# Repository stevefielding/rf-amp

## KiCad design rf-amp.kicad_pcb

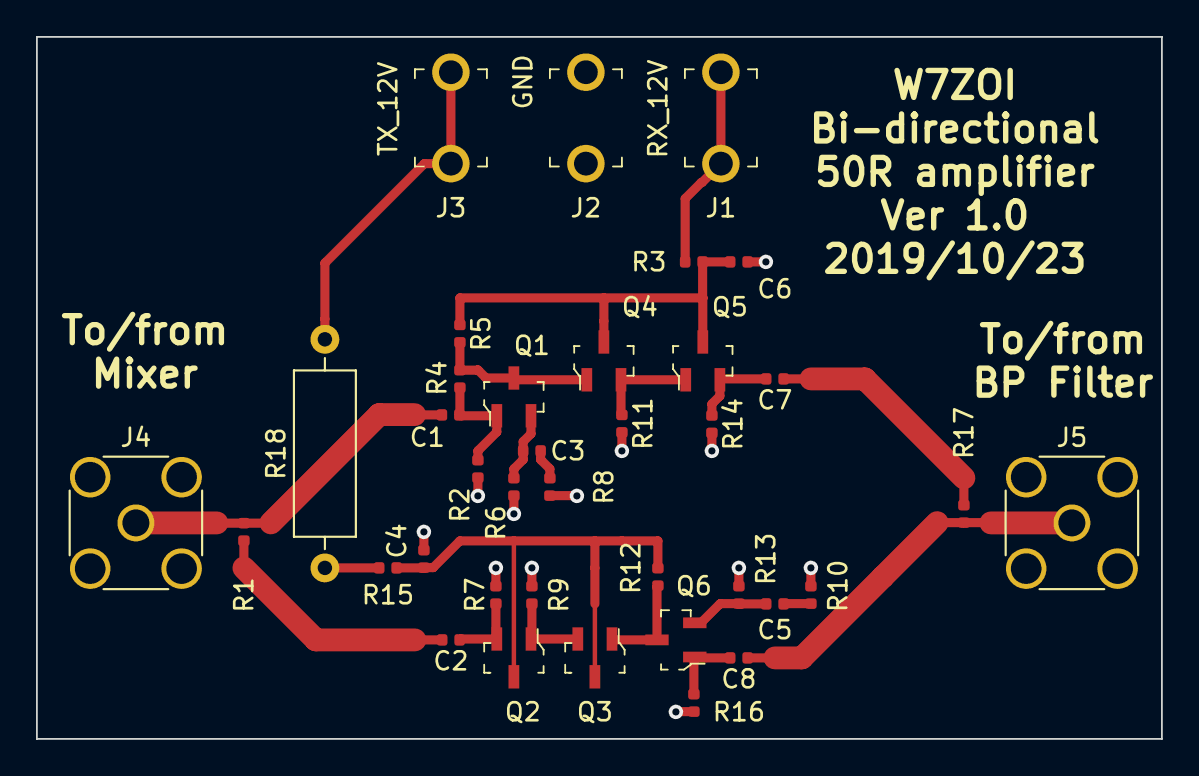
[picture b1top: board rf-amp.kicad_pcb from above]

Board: 2 copper layers, 62.5 x 39.0 mm, 37 parts (0 on the bottom side), 22 nets.

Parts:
C1, C2, C3, C4, C5, C6, C7, C8: C_Small; C_0402_1005Metric
J1, J3: 105-1102-001; Test_Jack_Horiz
J2: 105-1103-001; Test_Jack_Horiz
J4, J5: Conn_Coaxial; SMA_Amphenol_132134_Vertical
Q1, Q2, Q3, Q4, Q5, Q6: MMBT3904-TP; SOT-23-3
R1, R2, R3, R4, R5, R6, R7, R8, R9, R10, R11, R12, R13, R14, R15, R16, R17: R_Small_US; R_0402_1005Metric
R18: R_Small_US; R_Axial_DIN0309_L9.0mm_D3.2mm_P12.70mm_Horizontal

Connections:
GND: C4.1, C6.1, J2.1, J4.2, J5.2, R2.2, R6.2, R7.2, R8.2, R9.2, R10.2, R11.2, R13.2, R14.2, R16.2
unnamed: C1.1, Q1.1, R2.1, R4.2
unnamed: C1.2, J4.1, R1.1
unnamed: C2.1, Q2.2, R7.1
unnamed: C2.2, R1.2
unnamed: C3.1, R8.1
unnamed: C3.2, Q1.2, R6.1
unnamed: C4.2, Q2.3, Q3.3, R12.1, R15.2
unnamed: C5.1, Q6.2, R13.1
unnamed: C5.2, R10.1
unnamed: C6.2, Q4.3, Q5.3, R3.1, R5.1
unnamed: C7.1, R17.1
unnamed: C7.2, Q5.2, R14.1
unnamed: C8.1, J5.1, R17.2
unnamed: C8.2, Q6.1, R16.1
unnamed: J3.1, R18.2
unnamed: Q1.3, Q4.1, R4.1, R5.2
unnamed: Q2.1, Q3.2, R9.1
unnamed: Q3.1, Q6.3, R12.2
unnamed: Q4.2, Q5.1, R11.1
RX_12V: J1.1, R3.2
TX_12V: R15.1, R18.1

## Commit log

2019-10-24 Created
2019-10-29 Ver 1.0
